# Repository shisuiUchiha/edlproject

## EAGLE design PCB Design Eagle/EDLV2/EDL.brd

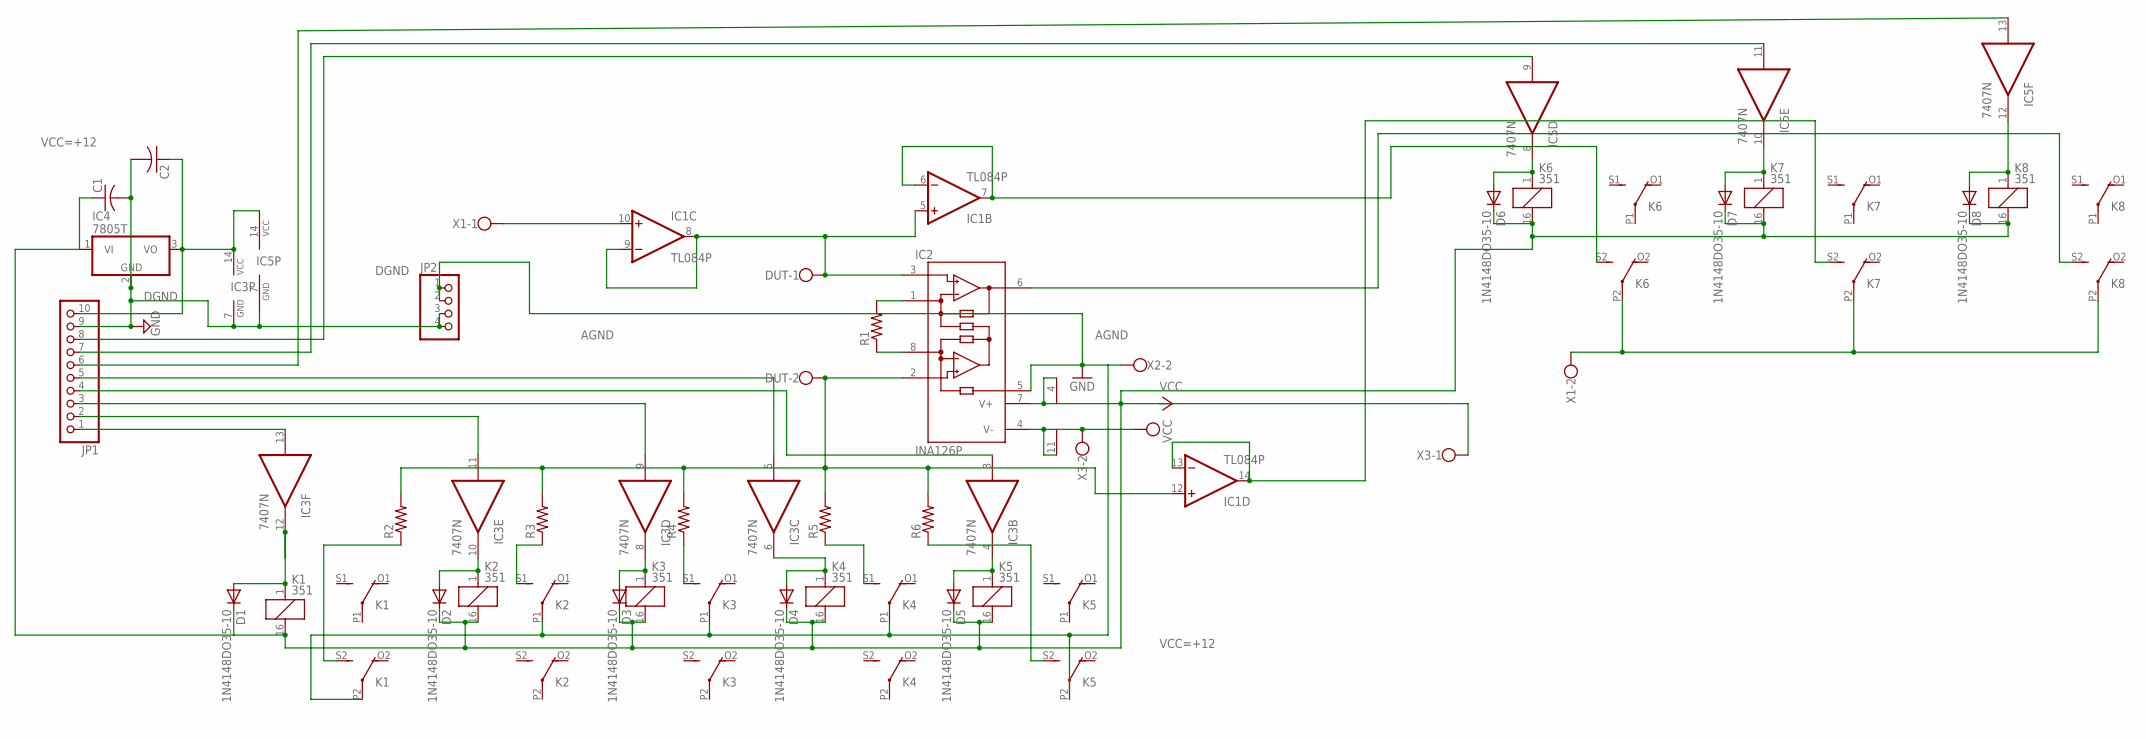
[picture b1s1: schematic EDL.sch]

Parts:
C1, C2: C-US050-024X044; C050-024X044
D1, D2, D3, D4, D5, D6, D7, D8: 1N4148DO35-10; DO35-10
DUT: W237-102
IC1: TL084P; DIL14
IC2: INA126P; DIL08
IC3, IC5: 7407N; DIL14
IC4: 7805T; TO220H
JP1: PINHD-1X10; 1X10
JP2: PINHD-1X4; 1X04
K1, K2, K3, K4, K5, K6, K7, K8: 351
R1, R2, R3, R4, R5, R6: R-US_0207/10; 0207/10
X1, X2, X3: W237-102

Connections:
+5: C2.1, IC3.14 (VCC), IC4.3 (VO), IC5.14 (VCC), JP1.10
AGND: IC2.5 (REF), JP2.1, JP2.2, K1.P2, K2.P1, K3.P1, K4.P1, K5.P2, X2.2
DGND: C1.2, C2.2, IC3.7 (GND), IC4.2 (GND), IC5.7 (GND), JP1.9, JP2.3, JP2.4
unnamed: DUT.1, IC1.5 (+IN), IC1.8 (OUT), IC1.9 (-IN), IC2.3 (+IN)
unnamed: IC1.10 (+IN), X1.1
unnamed: DUT.2, IC1.12 (+IN), IC2.2 (-IN), R2.2, R3.2, R4.2, R5.2, R6.2
unnamed: IC2.1 (RG), R1.2
unnamed: IC2.8 (RG), R1.1
unnamed: D1.A, IC3.12 (O), K1.1
unnamed: IC1.13 (-IN), IC1.14 (OUT), K7.S2 (S)
unnamed: D2.A, IC3.10 (O), K2.1
unnamed: D3.A, IC3.8 (O), K3.1
unnamed: D4.A, IC3.6 (O), K4.1
unnamed: D5.A, IC3.4 (O), K5.1
unnamed: K1.S2 (S), R2.1
unnamed: K2.S1 (S), R3.1
unnamed: K3.S1 (S), R4.1
unnamed: K4.S1 (S), R5.1
unnamed: K5.S2 (S), R6.1
unnamed: IC1.6 (-IN), IC1.7 (OUT), K6.S2 (S)
unnamed: IC5.11 (I), JP1.7
unnamed: IC5.13 (I), JP1.6
unnamed: IC5.9 (I), JP1.8
unnamed: IC2.6 (OUT), K8.S2 (S)
unnamed: K6.P2, K7.P2, K8.P2, X1.2
unnamed: IC3.13 (I), JP1.1
unnamed: IC3.11 (I), JP1.2
unnamed: IC3.9 (I), JP1.3
unnamed: IC3.5 (I), JP1.5
unnamed: IC3.3 (I), JP1.4
unnamed: D6.A, IC5.8 (O), K6.1
unnamed: D7.A, IC5.10 (O), K7.1
unnamed: D8.A, IC5.12 (O), K8.1
VCC(-12): IC1.11 (V-), IC2.4 (V-), X3.2
VCC=+12: C1.1, D1.C, D2.C, D3.C, D4.C, D5.C, IC4.1 (VI), K1.16 (2), K2.16 (2), K3.16 (2), K4.16 (2), K5.16 (2)
VSS: D6.C, D7.C, D8.C, IC1.4 (V+), IC2.7 (V+), K6.16 (2), K7.16 (2), K8.16 (2), X3.1

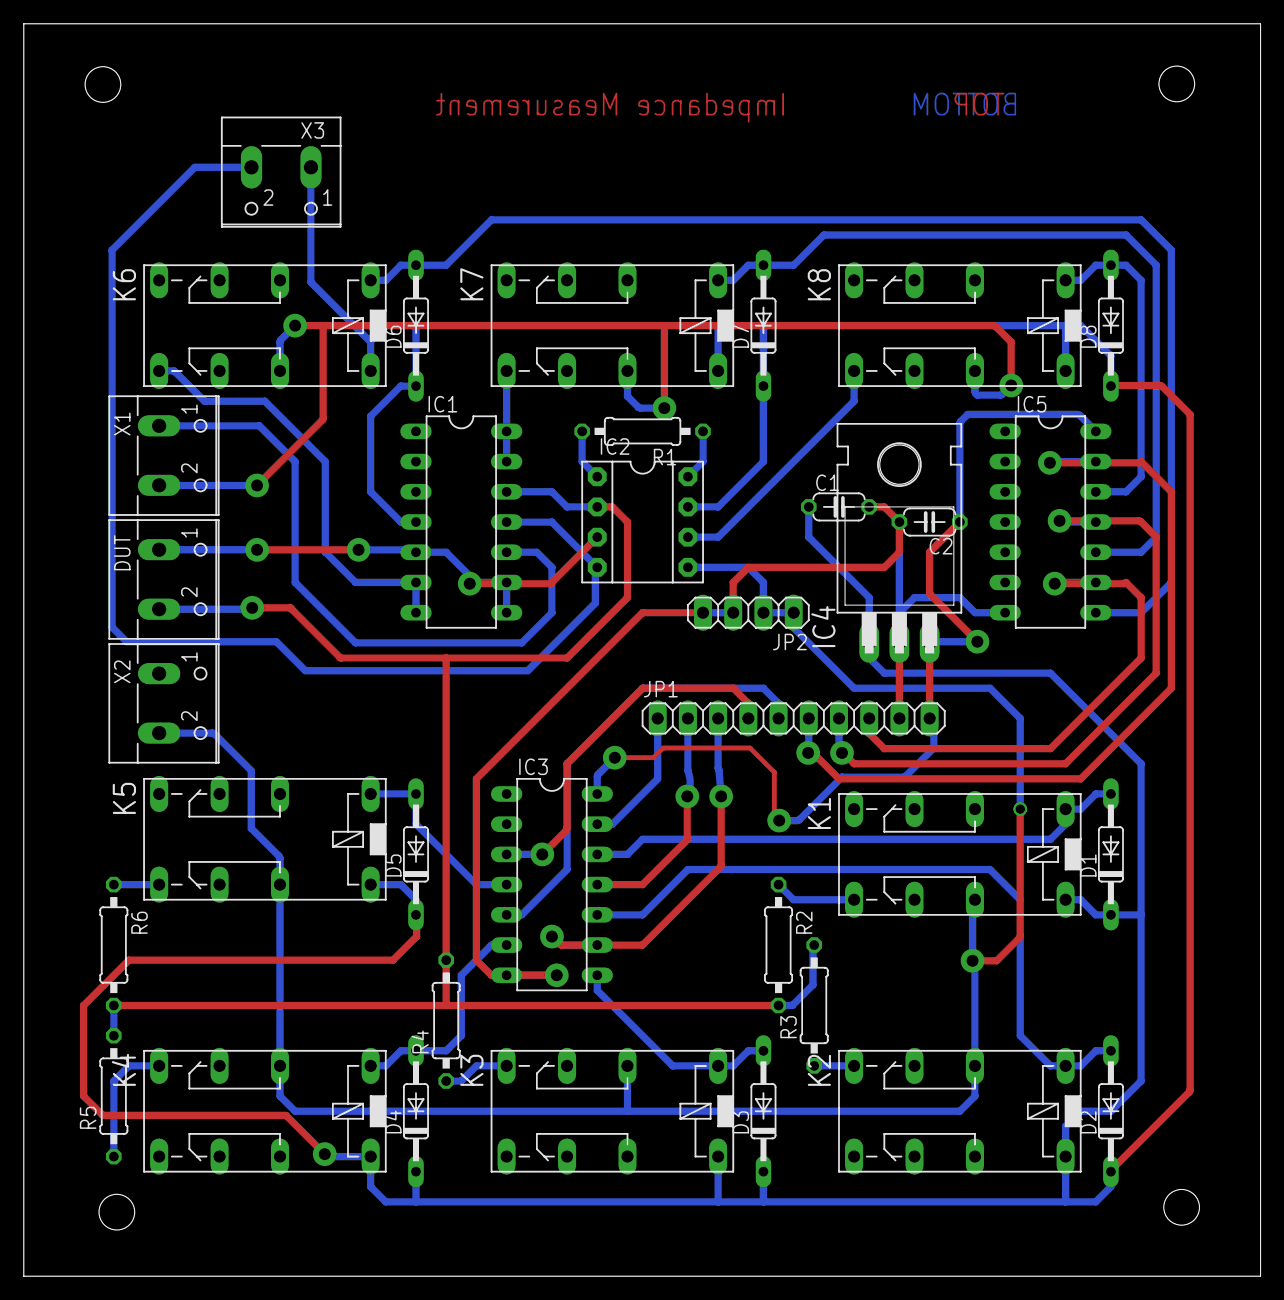
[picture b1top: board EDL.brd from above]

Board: 2 copper layers, 104.0 x 105.3 mm, 35 parts (0 on the bottom side), 36 nets.
